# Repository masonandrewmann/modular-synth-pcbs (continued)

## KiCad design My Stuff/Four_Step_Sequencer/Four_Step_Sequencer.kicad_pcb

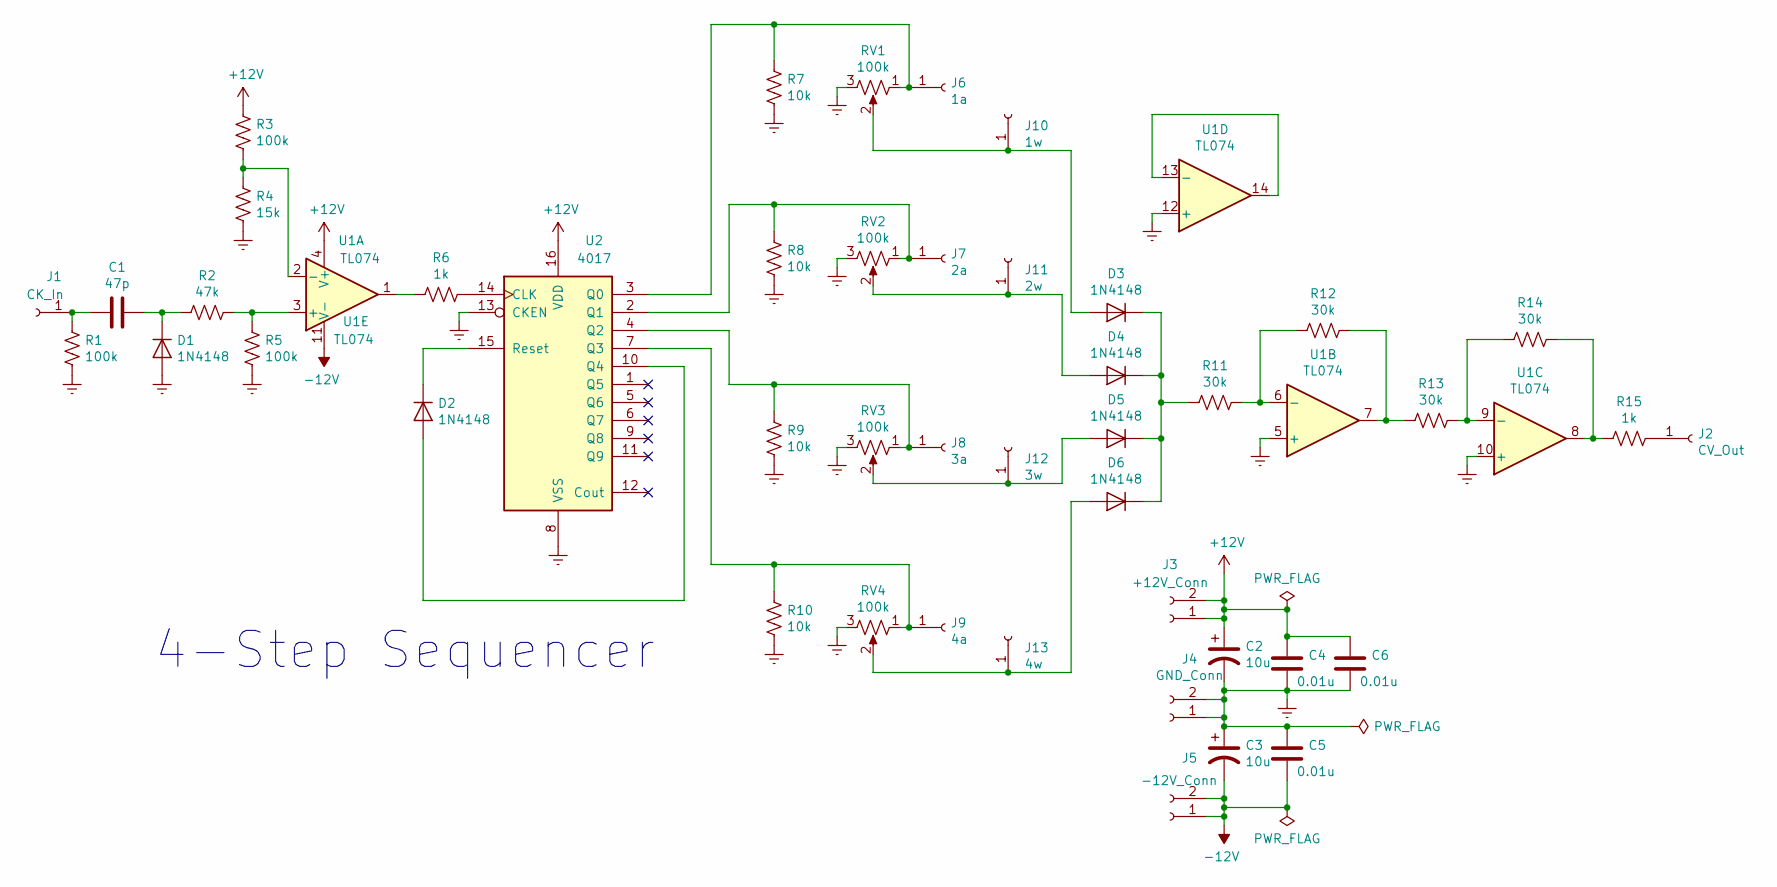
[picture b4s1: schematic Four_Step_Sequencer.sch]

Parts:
C1: 47p; C_Rect_L7.0mm_W2.5mm_P5.00mm
C2, C3: 10u; CP_Radial_D6.3mm_P2.50mm
C4, C5, C6: 0.01u; C_Rect_L7.0mm_W2.5mm_P5.00mm
D1, D2, D3, D4, D5, D6: 1N4148; D_T-1_P5.08mm_Horizontal
J1: CK_In; SolderWirePad_1x01_Drill1mm
J2: CV_Out; SolderWirePad_1x01_Drill1mm
J3: +12V_Conn; SolderWirePad_1x02_P3.81mm_Drill1mm
J4: GND_Conn; SolderWirePad_1x02_P3.81mm_Drill1mm
J5: -12V_Conn; SolderWirePad_1x02_P3.81mm_Drill1mm
J6: 1a; SolderWirePad_1x01_Drill1mm
J7: 2a; SolderWirePad_1x01_Drill1mm
J8: 3a; SolderWirePad_1x01_Drill1mm
J9: 4a; SolderWirePad_1x01_Drill1mm
J10: 1w; SolderWirePad_1x01_Drill1mm
J11: 2w; SolderWirePad_1x01_Drill1mm
J12: 3w; SolderWirePad_1x01_Drill1mm
J13: 4w; SolderWirePad_1x01_Drill1mm
R1, R3, R5: 100k; R_Axial_DIN0207_L6.3mm_D2.5mm_P7.62mm_Horizontal
R2: 47k; R_Axial_DIN0207_L6.3mm_D2.5mm_P7.62mm_Horizontal
R4: 15k; R_Axial_DIN0207_L6.3mm_D2.5mm_P7.62mm_Horizontal
R6, R15: 1k; R_Axial_DIN0207_L6.3mm_D2.5mm_P7.62mm_Horizontal
R7, R8, R9, R10: 10k; R_Axial_DIN0207_L6.3mm_D2.5mm_P7.62mm_Horizontal
R11, R12, R13, R14: 30k; R_Axial_DIN0207_L6.3mm_D2.5mm_P7.62mm_Horizontal
RV1, RV2, RV3, RV4: 100k
U1: TL074; DIP-14_W7.62mm_Socket
U2: 4017; DIP-16_W7.62mm_Socket

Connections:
+12V: C2.1, C4.1, C6.1, J3.1, J3.2, R3.1, U1.4 (V+), U2.16 (VDD)
-12V: C3.2, C5.2, J5.1, J5.2, U1.11 (V-)
Earth: C2.2, C3.1, C4.2, C5.1, C6.2, D1.2 (A), J4.1, J4.2, R1.1, R4.2, R5.2, R7.2, R8.2, R9.2, R10.2, RV1.3, RV2.3, RV3.3, RV4.3, U1.5 (+), U1.10 (+), U1.12 (+), U2.8 (VSS), U2.13 (CKEN)
unnamed: C1.1, D1.1 (K), R2.1
unnamed: C1.2, J1.1, R1.2
unnamed: D2.1 (K), U2.15 (Reset)
unnamed: D2.2 (A), U2.10 (Q4)
unnamed: D3.1 (K), D4.1 (K), D5.1 (K), D6.1 (K), R11.2
unnamed: D3.2 (A), J10.1, RV1.2
unnamed: D4.2 (A), J11.1, RV2.2
unnamed: D5.2 (A), J12.1, RV3.2
unnamed: D6.2 (A), J13.1, RV4.2
unnamed: J2.1, R15.1
unnamed: J6.1, R7.1, RV1.1, U2.3 (Q0)
unnamed: J7.1, R8.1, RV2.1, U2.2 (Q1)
unnamed: J8.1, R9.1, RV3.1, U2.4 (Q2)
unnamed: J9.1, R10.1, RV4.1, U2.7 (Q3)
unnamed: R2.2, R5.1, U1.3 (+)
unnamed: R3.2, R4.1, U1.2 (-)
unnamed: R6.1, U1.1
unnamed: R6.2, U2.14 (CLK)
unnamed: R11.1, R12.2, U1.6 (-)
unnamed: R12.1, R13.2, U1.7
unnamed: R13.1, R14.2, U1.9 (-)
unnamed: R14.1, R15.2, U1.8
unnamed: U1.13 (-), U1.14

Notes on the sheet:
4-Step Sequencer

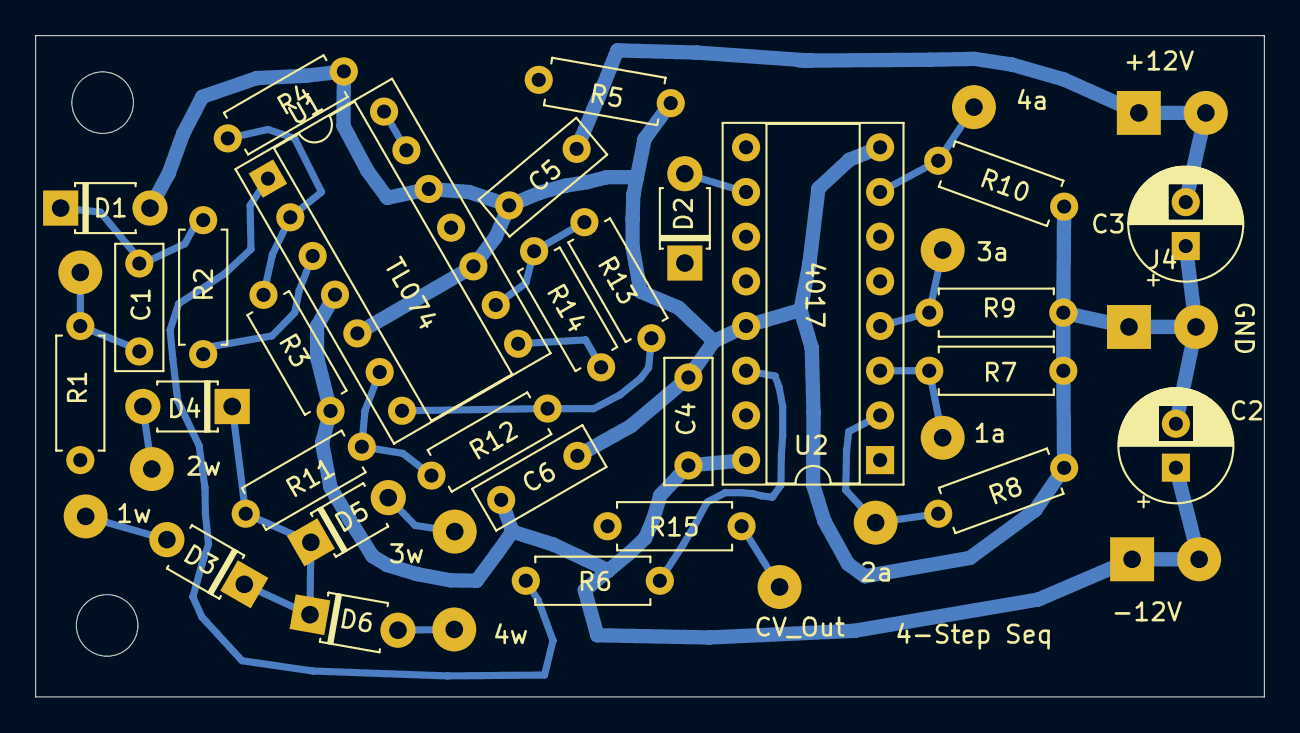
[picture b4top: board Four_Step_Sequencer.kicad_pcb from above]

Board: 2 copper layers, 69.8 x 37.6 mm, 42 parts (0 on the bottom side), 26 nets.

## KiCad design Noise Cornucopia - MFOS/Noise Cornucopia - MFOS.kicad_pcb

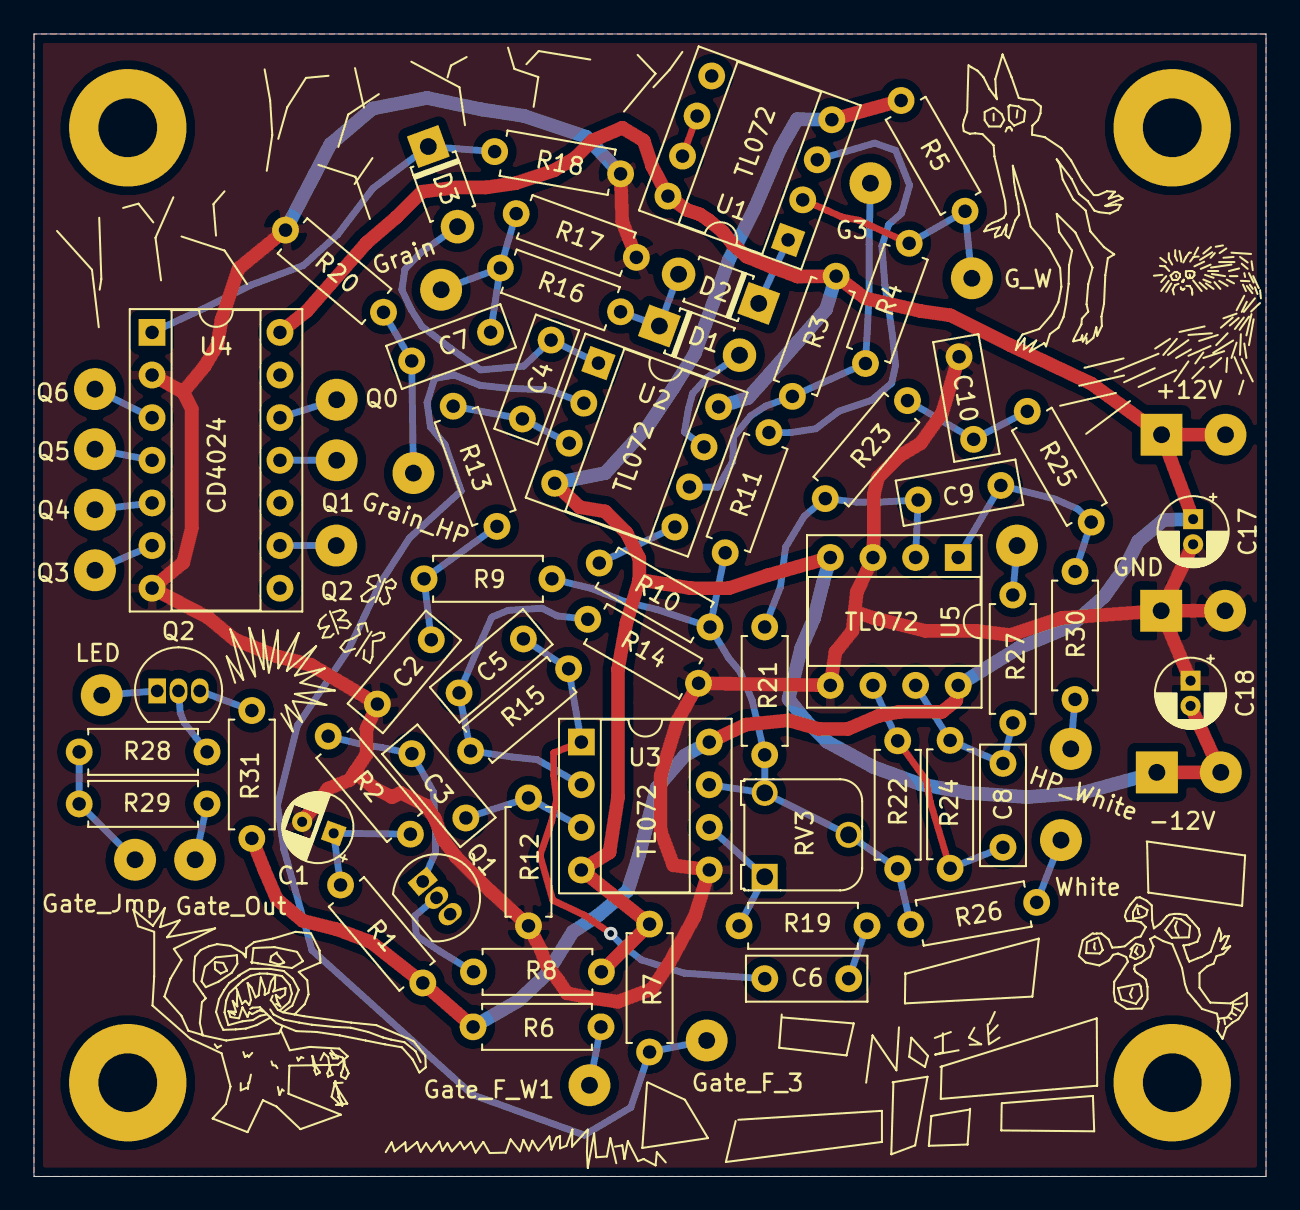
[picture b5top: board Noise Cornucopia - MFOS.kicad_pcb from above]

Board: 2 copper layers, 73.4 x 68.1 mm, 76 parts (0 on the bottom side), 48 nets.

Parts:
C1: 1u; CP_Radial_D4.0mm_P2.00mm
C2: 0.0047u; C_Rect_L7.0mm_W2.5mm_P5.00mm
C3, C6: 0.1u; C_Rect_L7.0mm_W2.5mm_P5.00mm
C4, C5: 10p; C_Rect_L7.0mm_W2.5mm_P5.00mm
C7, C8: 0.001u; C_Rect_L7.0mm_W2.5mm_P5.00mm
C9: 100p; C_Rect_L7.0mm_W2.5mm_P5.00mm
C10: 0.01u; C_Rect_L7.0mm_W2.5mm_P5.00mm
C17, C18: 10u; CP_Radial_D4.0mm_P1.50mm
D1, D2, D3: D; D_T-1_P5.08mm_Horizontal
J1: GRNS_3; SolderWirePad_1x01_Drill1mm
J2: GRNS_W1; SolderWirePad_1x01_Drill1mm
J3: Gate_F_W1; SolderWirePad_1x01_Drill1mm
J4: Gate_F_3; SolderWirePad_1x01_Drill1mm
J5: Grain; SolderWirePad_1x01_Drill1mm
J6: Grain_HP; SolderWirePad_1x01_Drill1mm
J7: Q0; SolderWirePad_1x01_Drill1mm
J8: Q1; SolderWirePad_1x01_Drill1mm
J9: Q2; SolderWirePad_1x01_Drill1mm
J10: Q3; SolderWirePad_1x01_Drill1mm
J11: Q4; SolderWirePad_1x01_Drill1mm
J12: Q5; SolderWirePad_1x01_Drill1mm
J13: Q6; SolderWirePad_1x01_Drill1mm
J14: GATE_JMP; SolderWirePad_1x01_Drill1mm
J15: White; SolderWirePad_1x01_Drill1mm
J16: LP_White; SolderWirePad_1x01_Drill1mm
J17: GATE_OUT; SolderWirePad_1x01_Drill1mm
J18: HP_White; SolderWirePad_1x01_Drill1mm
J19: LED; SolderWirePad_1x01_Drill1mm
J20: +12V_Conn; SolderWirePad_1x02_P3.81mm_Drill1mm
J21: GND_Conn?; SolderWirePad_1x02_P3.81mm_Drill1mm
J22: -12V_Conn; SolderWirePad_1x02_P3.81mm_Drill1mm
Q1, Q2: 2N3904; TO-92_Inline
R1, R2, R15, R21: 470k; R_Axial_DIN0207_L6.3mm_D2.5mm_P7.62mm_Horizontal
R3, R5, R6, R28: 47k; R_Axial_DIN0207_L6.3mm_D2.5mm_P7.62mm_Horizontal
R4: 200k; R_Axial_DIN0207_L6.3mm_D2.5mm_P7.62mm_Horizontal
R7, R9, R13, R18: 20k; R_Axial_DIN0207_L6.3mm_D2.5mm_P7.62mm_Horizontal
R8, R10, R11, R14, R19: 10k; R_Axial_DIN0207_L6.3mm_D2.5mm_P7.62mm_Horizontal
R12: 2M; R_Axial_DIN0207_L6.3mm_D2.5mm_P7.62mm_Horizontal
R16, R17, R20, R31: 4k7; R_Axial_DIN0207_L6.3mm_D2.5mm_P7.62mm_Horizontal
R22: 100k; R_Axial_DIN0207_L6.3mm_D2.5mm_P7.62mm_Horizontal
R23, R25: 43k; R_Axial_DIN0207_L6.3mm_D2.5mm_P7.62mm_Horizontal
R24: 1M; R_Axial_DIN0207_L6.3mm_D2.5mm_P7.62mm_Horizontal
R26, R27, R29, R30: 1k; R_Axial_DIN0207_L6.3mm_D2.5mm_P7.62mm_Horizontal
RV3: 500k; Potentiometer_Runtron_RM-065_Vertical
U1, U2, U3, U5: TL072; DIP-8_W7.62mm_Socket
U4: 4024; DIP-14_W7.62mm_Socket

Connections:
+12V: C17.1, J20.1, J20.2, R1.1, R3.2, R6.2, R31.2, U1.8, U2.8, U3.8, U4.14, U5.8
-12V: C18.2, J22.1, J22.2, R5.1, R7.1, R8.2, U1.4, U2.4, U3.4, U5.4
Earth: C1.2, C2.2, C10.1, C17.2, C18.1, J21.1, J21.2, R12.2, R14.2, R17.1, R18.1, R20.1, U3.5, U4.2, U4.7, U5.3, U5.5
unnamed: C1.1, R1.2, R2.1
unnamed: C2.1, R9.1, R13.1
unnamed: C3.1, R12.1, U3.3
unnamed: C3.2, Q1.1, R2.2
unnamed: C4.1, D3.2, U2.1
unnamed: C4.2, R13.2, U2.3
unnamed: C5.1, C6.2, R15.1, U3.1
unnamed: C5.2, R14.1, R15.2, U3.2
unnamed: C6.1, R19.2
unnamed: C7.1, J6.1, R20.2
unnamed: C7.2, J5.1, R16.1, R17.2
unnamed: C8.1, R24.1, R27.2, U5.7
unnamed: C8.2, R22.1, R24.2, U5.6
unnamed: C9.1, R25.1, R30.2, U5.1
unnamed: C9.2, R21.1, R23.2, U5.2
unnamed: C10.2, R23.1, R25.2
unnamed: D1.1, D2.2, R16.2
unnamed: D1.2, U2.7
unnamed: D2.1, U1.1
unnamed: D3.1, R18.2, U4.1
unnamed: J19.1, Q2.1
unnamed: J1.1, R3.1, R4.2, U2.6
unnamed: J2.1, R4.1, R5.2, U1.2
unnamed: J3.1, R6.1
unnamed: J4.1, R7.2, U2.2
unnamed: J7.1, U4.12
unnamed: J8.1, U4.11
unnamed: J9.1, U4.9
unnamed: J10.1, U4.6
unnamed: J11.1, U4.5
unnamed: J12.1, U4.4
unnamed: J13.1, U4.3
unnamed: J14.1, R28.1, R29.1
unnamed: J15.1, R26.1
unnamed: J16.1, R27.1
unnamed: J17.1, R29.2
unnamed: J18.1, R30.1
unnamed: Q1.2, R8.1
unnamed: Q2.2, R28.2
unnamed: Q2.3, R31.1
unnamed: R10.1, U2.5
unnamed: R9.2, R10.2, R11.2, R21.2, R22.2, R26.2, RV3.2, RV3.3, U3.7
unnamed: R11.1, U1.3
unnamed: R19.1, RV3.1, U3.6
unnamed: U1.6, U1.7

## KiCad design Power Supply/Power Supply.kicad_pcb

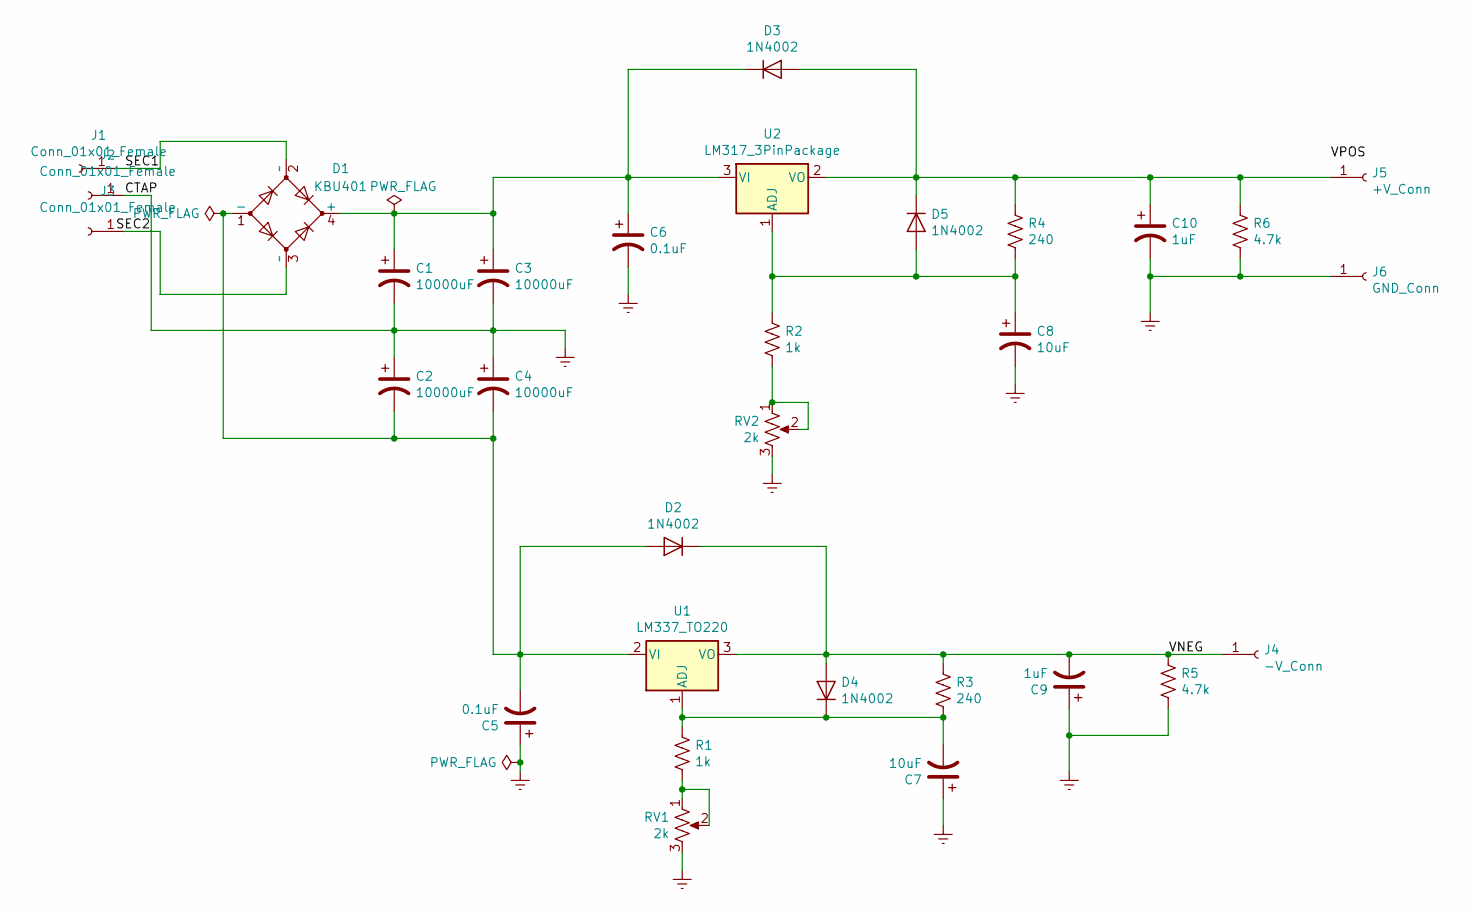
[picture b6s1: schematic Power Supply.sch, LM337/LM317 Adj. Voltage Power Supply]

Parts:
C1, C2, C3, C4: 10000uF; CP_Radial_D30.0mm_P10.00mm_SnapIn
C5, C6: 0.1uF; CP_Radial_D5.0mm_P2.50mm
C7, C8: 10uF; CP_Radial_D5.0mm_P2.50mm
C9, C10: 1uF; CP_Radial_D5.0mm_P2.50mm
D1: KBU401; Diode_Bridge_Vishay_KBU
D2, D3, D4, D5: 1N4002; D_DO-41_SOD81_P10.16mm_Horizontal
J1, J2, J3: Conn_01x01_Female; Pin_D1.1mm_L10.2mm_W3.5mm_Flat
J4: -V_Conn; Pin_D1.1mm_L10.2mm_W3.5mm_Flat
J5: +V_Conn; Pin_D1.1mm_L10.2mm_W3.5mm_Flat
J6: GND_Conn; Pin_D1.1mm_L10.2mm_W3.5mm_Flat
R1, R2: 1k; R_Axial_DIN0207_L6.3mm_D2.5mm_P7.62mm_Horizontal
R3, R4: 240; R_Axial_DIN0207_L6.3mm_D2.5mm_P7.62mm_Horizontal
R5, R6: 4.7k; R_Axial_DIN0207_L6.3mm_D2.5mm_P7.62mm_Horizontal
RV1, RV2: 2k; Potentiometer_Runtron_RM-065_Vertical
U1: LM337_TO220; TO-220-3_Horizontal_TabUp_WIDE
U2: LM317_3PinPackage; TO-220-3_Horizontal_TabDown_WIDE

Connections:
/SEC1: D1.2 (~~), J1.1
/VNEG: C9.2, D2.1 (K), D4.2 (A), J4.1, R3.1, R5.1, U1.3 (VO)
Earth: C1.2, C2.1, C3.2, C4.1, C5.1, C6.2, C7.1, C8.2, C9.1, C10.2, J2.1, J6.1, R5.2, R6.2, RV1.3, RV2.3
unnamed: C1.1, C3.1, C6.1, D1.4 (+), D3.1 (K), U2.3 (VI)
unnamed: C2.2, C4.2, C5.2, D1.1 (-), D2.2 (A), U1.2 (VI)
unnamed: C7.2, D4.1 (K), R1.1, R3.2, U1.1 (ADJ)
unnamed: C8.1, D5.2 (A), R2.1, R4.2, U2.1 (ADJ)
unnamed: C10.1, D3.2 (A), D5.1 (K), J5.1, R4.1, R6.1, U2.2 (VO)
unnamed: D1.3 (~~), J3.1
unnamed: R1.2, RV1.1, RV1.2
unnamed: R2.2, RV2.1, RV2.2

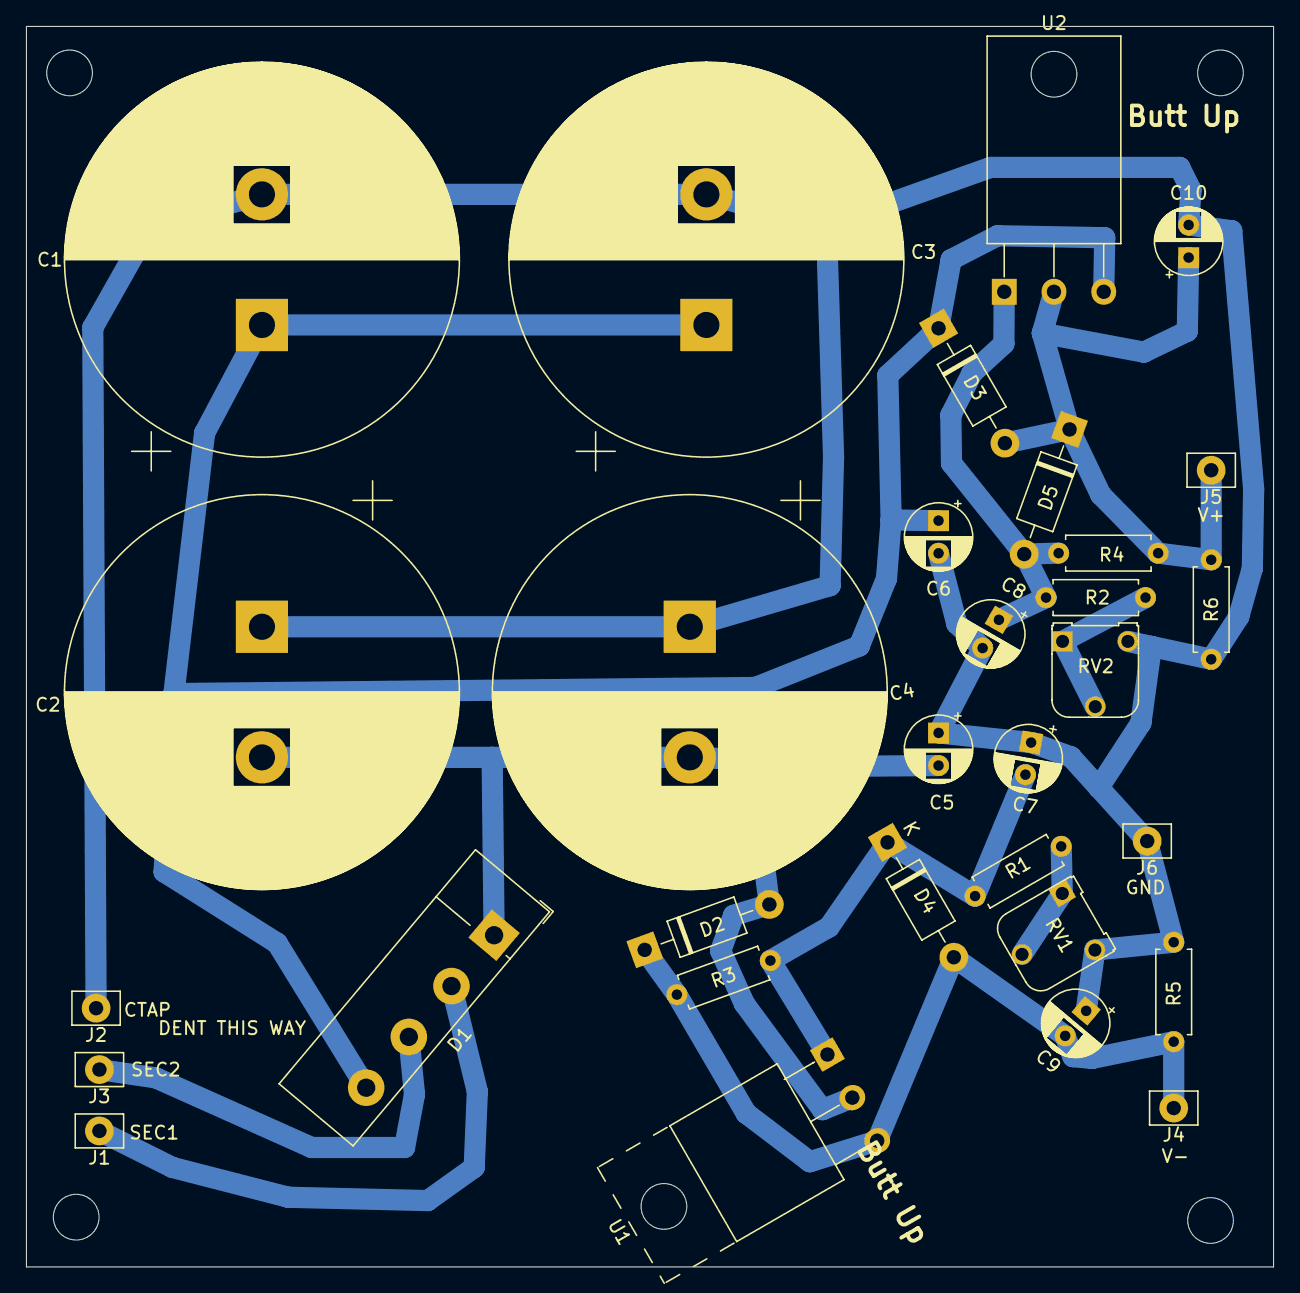
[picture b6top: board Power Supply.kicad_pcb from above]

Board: 2 copper layers, 95.5 x 95.0 mm, 31 parts (0 on the bottom side), 11 nets.

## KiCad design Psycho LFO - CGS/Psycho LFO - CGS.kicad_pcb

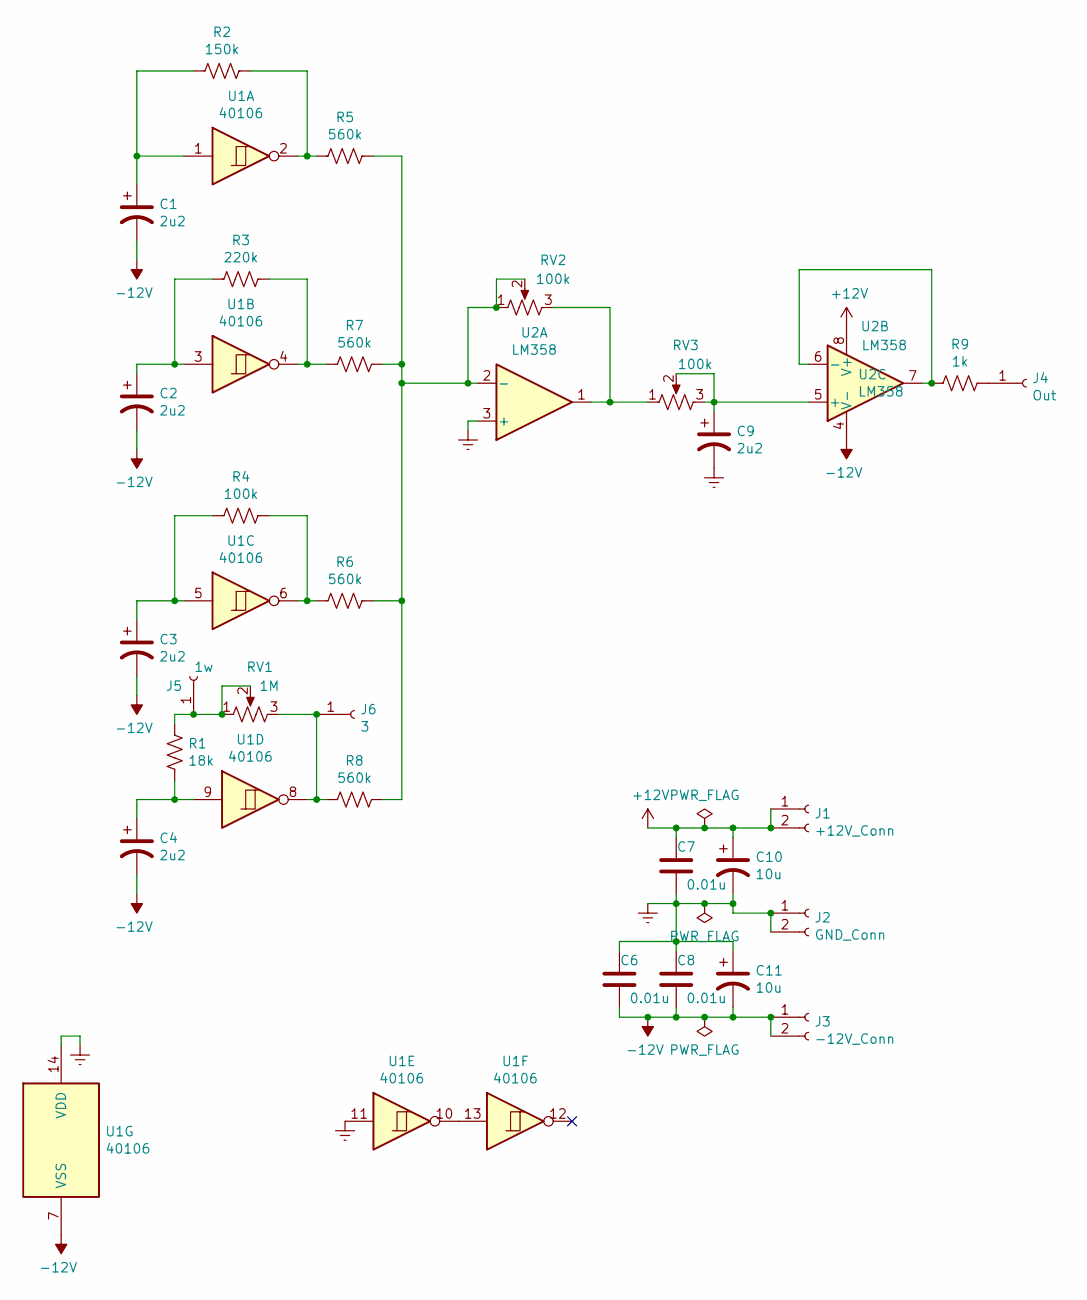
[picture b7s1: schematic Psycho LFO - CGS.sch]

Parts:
C1, C2, C3, C4, C9: 2u2; CP_Radial_D5.0mm_P2.50mm
C6, C7, C8: 0.01u; C_Rect_L7.0mm_W2.5mm_P5.00mm
C10, C11: 10u; CP_Radial_D6.3mm_P2.50mm
J1: +12V_Conn; SolderWirePad_1x02_P3.81mm_Drill1mm
J2: GND_Conn; SolderWirePad_1x02_P3.81mm_Drill1mm
J3: -12V_Conn; SolderWirePad_1x02_P3.81mm_Drill1mm
J4: Out; SolderWirePad_1x01_Drill1mm
J5: 1w; SolderWirePad_1x01_Drill1mm
J6: 3; SolderWirePad_1x01_Drill1mm
R1: 18k; R_Axial_DIN0207_L6.3mm_D2.5mm_P7.62mm_Horizontal
R2: 150k; R_Axial_DIN0207_L6.3mm_D2.5mm_P7.62mm_Horizontal
R3: 220k; R_Axial_DIN0207_L6.3mm_D2.5mm_P7.62mm_Horizontal
R4: 100k; R_Axial_DIN0207_L6.3mm_D2.5mm_P7.62mm_Horizontal
R5, R6, R7, R8: 560k; R_Axial_DIN0207_L6.3mm_D2.5mm_P7.62mm_Horizontal
R9: 1k; R_Axial_DIN0207_L6.3mm_D2.5mm_P7.62mm_Horizontal
RV1: 1M
RV2, RV3: 100k
U1: 40106; DIP-14_W7.62mm_Socket
U2: LM358; DIP-8_W7.62mm_Socket

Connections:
+12V: C7.1, C10.1, J1.1, J1.2, U2.8 (V+)
-12V: C1.2, C2.2, C3.2, C4.2, C6.2, C8.2, C11.2, J3.1, J3.2, U1.7 (VSS), U2.4 (V-)
Earth: C6.1, C7.2, C8.1, C9.2, C10.2, C11.1, J2.1, J2.2, U1.11, U1.14 (VDD), U2.3 (+)
unnamed: C1.1, R2.2, U1.1
unnamed: C2.1, R3.2, U1.3
unnamed: C3.1, R4.2, U1.5
unnamed: C4.1, R1.1, U1.9
unnamed: C9.1, RV3.2, RV3.3, U2.5 (+)
unnamed: J4.1, R9.1
unnamed: J5.1, R1.2, RV1.1, RV1.2
unnamed: J6.1, R8.2, RV1.3, U1.8
unnamed: R2.1, R5.2, U1.2
unnamed: R3.1, R7.2, U1.4
unnamed: R4.1, R6.2, U1.6
unnamed: R5.1, R6.1, R7.1, R8.1, RV2.1, RV2.2, U2.2 (-)
unnamed: R9.2, U2.6 (-), U2.7
unnamed: RV2.3, RV3.1, U2.1
unnamed: U1.10, U1.13

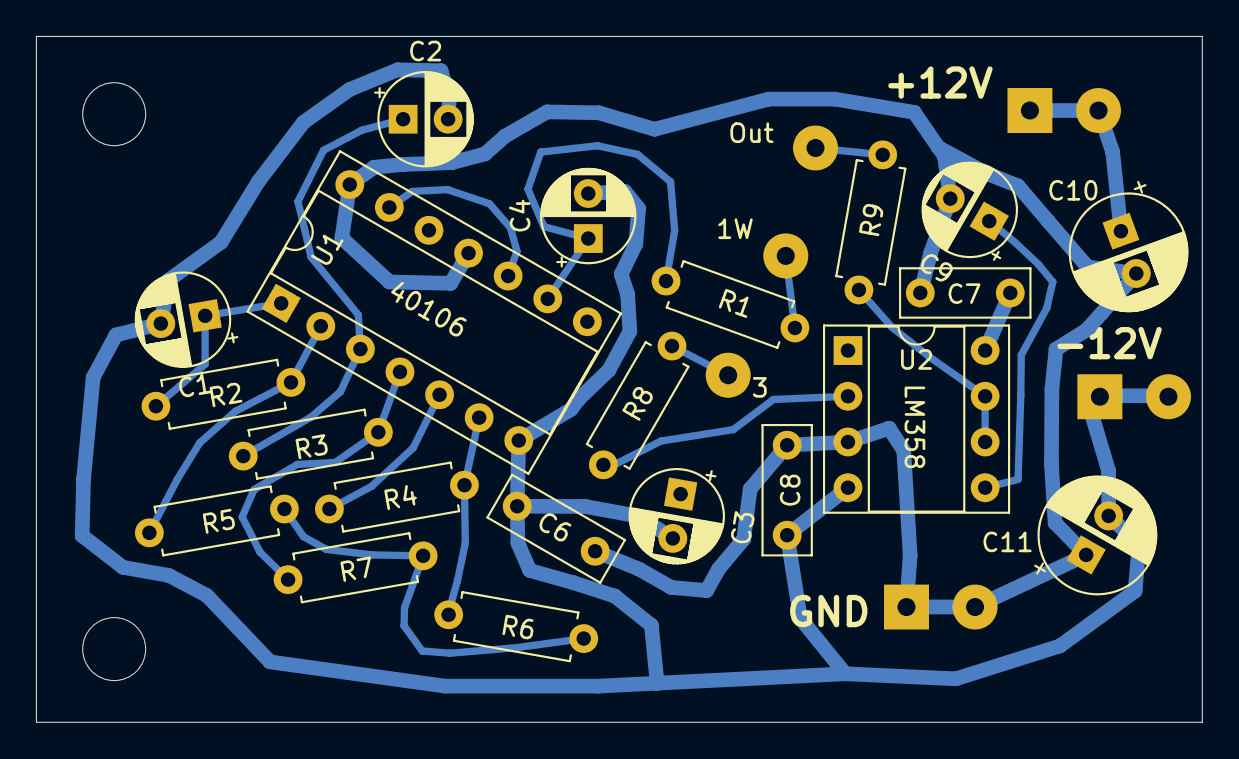
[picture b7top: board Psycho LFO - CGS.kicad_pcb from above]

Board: 2 copper layers, 64.8 x 38.1 mm, 27 parts (0 on the bottom side), 17 nets.

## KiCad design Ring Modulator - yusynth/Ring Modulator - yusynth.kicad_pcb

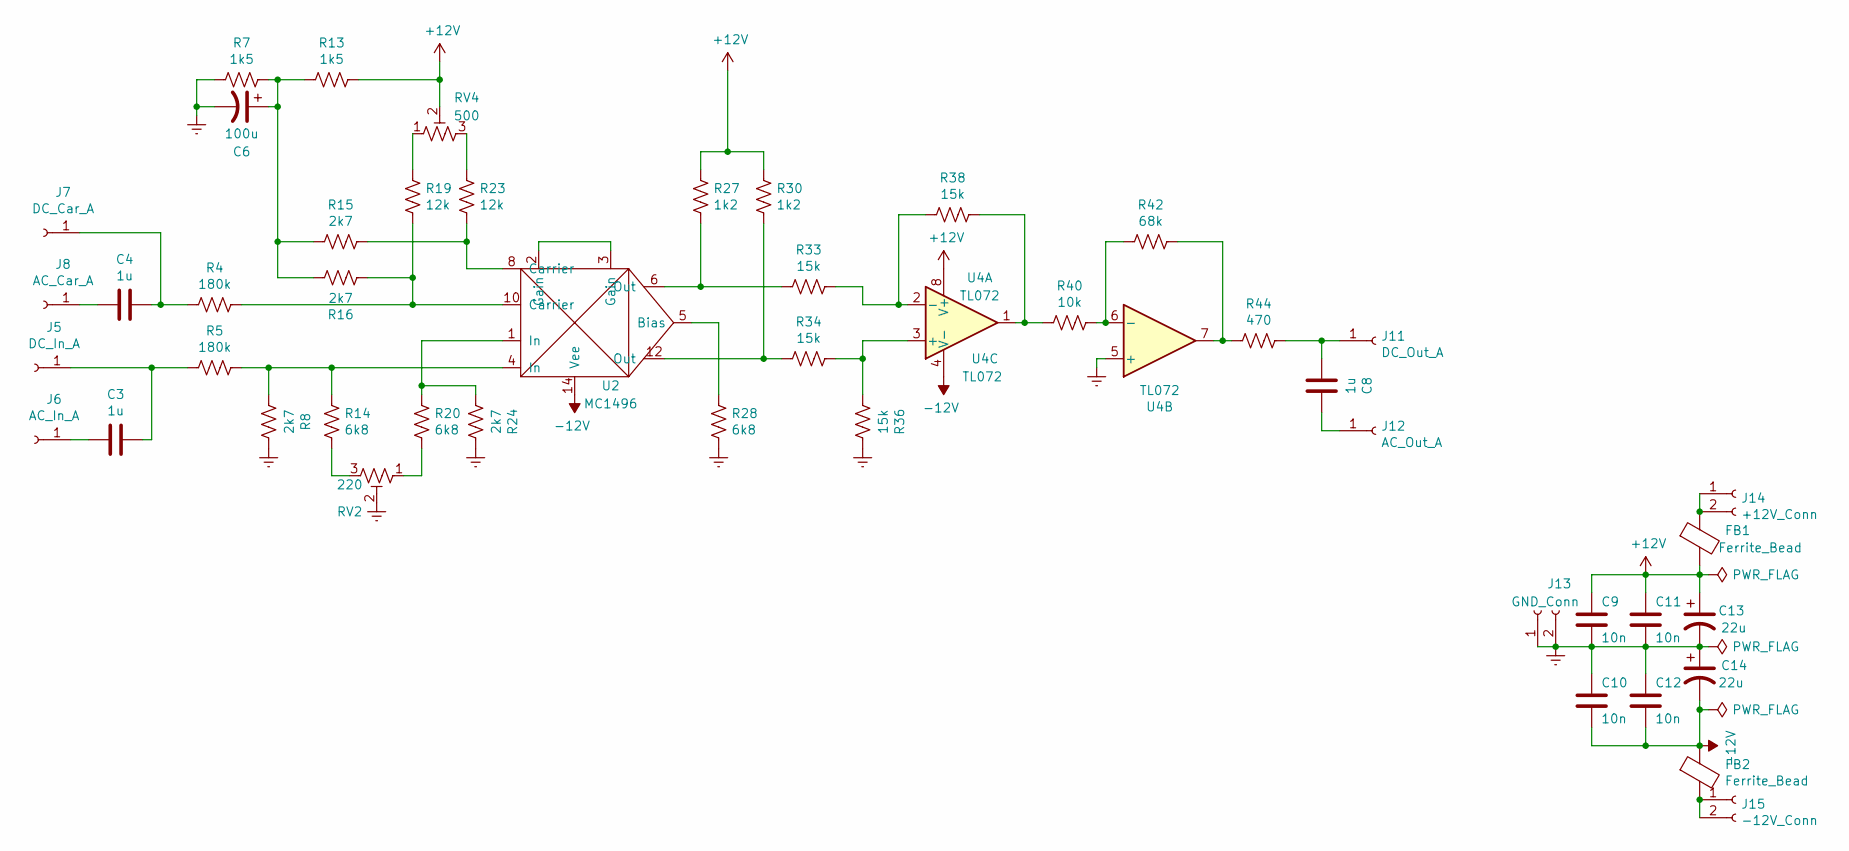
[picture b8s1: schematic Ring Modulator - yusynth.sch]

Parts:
C3, C4: 1u; C_0603_1608Metric; LCSC C15849
C6: 100u; CP_Radial_D6.3mm_P2.50mm
C8: 1u; C_0603_1608Metric; JLCPCB LCSC
C9, C10, C11, C12: 10n; C_0603_1608Metric; LCSC C57112
C13, C14: 22u; CP_Radial_D6.3mm_P2.50mm
FB1, FB2: Ferrite_Bead; L_Axial_L7.0mm_D3.3mm_P10.16mm_Horizontal_Fastron_MICC
J5: DC_In_A; SolderWirePad_1x01_Drill1mm
J6: AC_In_A; SolderWirePad_1x01_Drill1mm
J7: DC_Car_A; SolderWirePad_1x01_Drill1mm
J8: AC_Car_A; SolderWirePad_1x01_Drill1mm
J11: DC_Out_A; SolderWirePad_1x01_Drill1mm
J12: AC_Out_A; SolderWirePad_1x01_Drill1mm
J13: GND_Conn; SolderWirePad_1x02_P3.81mm_Drill1mm
J14: +12V_Conn; SolderWirePad_1x02_P3.81mm_Drill1mm
J15: -12V_Conn; SolderWirePad_1x02_P3.81mm_Drill1mm
R4, R5: 180k; R_0603_1608Metric; LCSC C22827
R7, R13: 1k5; R_0603_1608Metric; LCSC C22843
R8, R15, R16, R24: 2k7; R_0603_1608Metric; LCSC C13167
R14, R20, R28: 6k8; R_0603_1608Metric; LCSC C23212
R19, R23: 12k; R_0603_1608Metric; LCSC C22790
R27, R30: 1k2; R_0603_1608Metric; LCSC C22765
R33, R34, R36, R38: 15k; R_0603_1608Metric; LCSC C22809
R40: 10k; R_0603_1608Metric; LCSC C25804
R42: 68k; R_0603_1608Metric; LCSC C23231
R44: 470; R_0603_1608Metric; LCSC C23179
RV2: 220; Potentiometer_Runtron_RM-065_Vertical
RV4: 500; Potentiometer_Runtron_RM-065_Vertical
U2: MC1496; DIP-14_W7.62mm_Socket
U4: TL072; SOIC-8_3.9x4.9mm_P1.27mm; LCSC C6961

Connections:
+12V: C9.1, C11.1, C13.1, FB1.2, R13.2, R27.1, R30.1, RV4.2, U4.8 (V+)
-12V: C10.2, C12.2, C14.2, FB2.1, U2.14 (Vee), U4.4 (V-)
Earth: C6.2, C9.2, C10.1, C11.2, C12.1, C13.2, C14.1, J13.1, J13.2, R7.1, R8.1, R24.1, R28.2, R36.1, RV2.2, U4.5 (+)
unnamed: C3.1, J5.1, R5.2
unnamed: C3.2, J6.1
unnamed: C4.1, J7.1, R4.2
unnamed: C4.2, J8.1
unnamed: C6.1, R7.2, R13.1, R15.2, R16.1
unnamed: C8.1, J12.1
unnamed: C8.2, J11.1, R44.1
unnamed: FB1.1, J14.1, J14.2
unnamed: FB2.2, J15.1, J15.2
unnamed: R5.1, R8.2, R14.1, U2.4 (In)
unnamed: R14.2, RV2.3
unnamed: R15.1, R23.1, U2.8 (Carrier)
unnamed: R4.1, R16.2, R19.1, U2.10 (Carrier)
unnamed: R19.2, RV4.1
unnamed: R20.1, R24.2, U2.1 (In)
unnamed: R20.2, RV2.1
unnamed: R23.2, RV4.3
unnamed: R27.2, R33.2, U2.6 (Out)
unnamed: R28.1, U2.5 (Bias)
unnamed: R30.2, R34.2, U2.12 (Out)
unnamed: R33.1, R38.2, U4.2 (-)
unnamed: R34.1, R36.2, U4.3 (+)
unnamed: R38.1, R40.2, U4.1
unnamed: R40.1, R42.2, U4.6 (-)
unnamed: R42.1, R44.2, U4.7
unnamed: U2.2 (Gain), U2.3 (Gain)

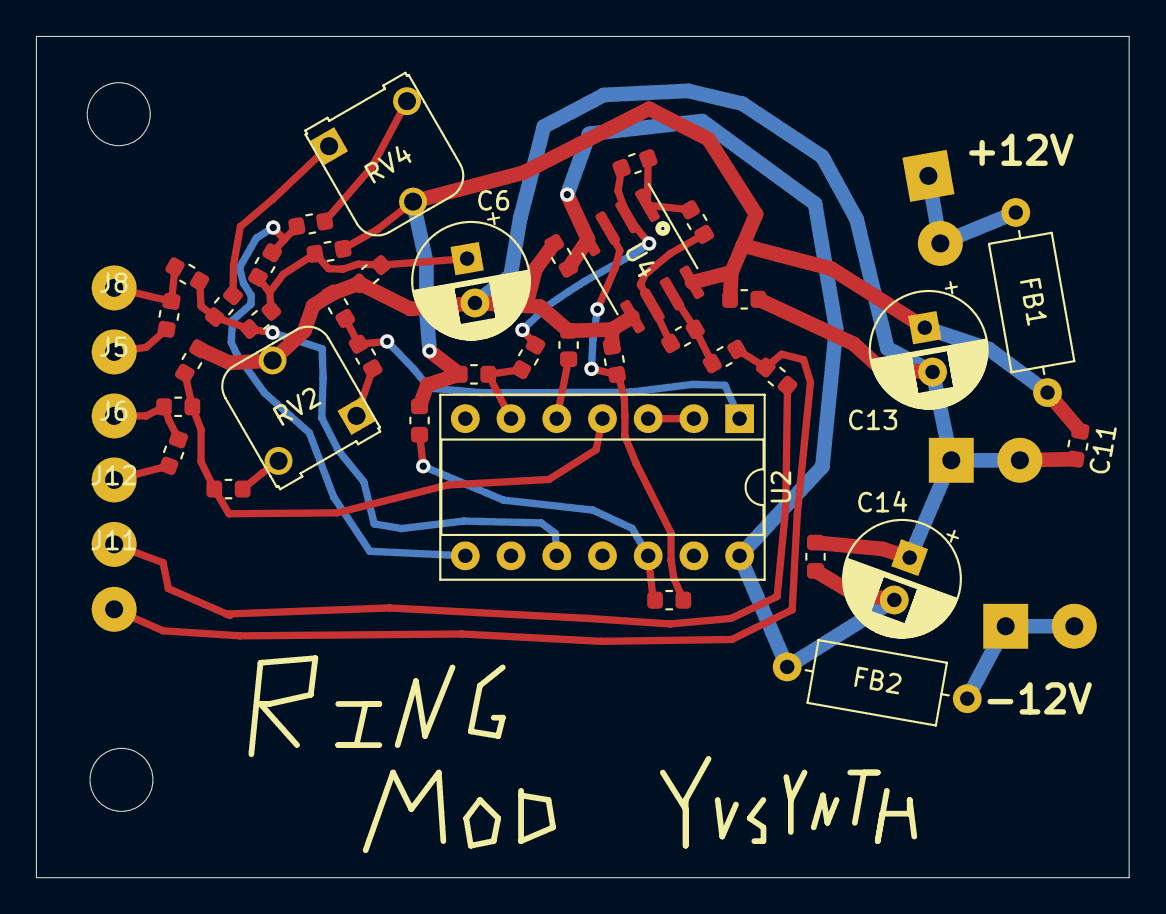
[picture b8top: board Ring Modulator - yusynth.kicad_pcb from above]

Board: 2 copper layers, 60.7 x 46.7 mm, 47 parts (0 on the bottom side), 29 nets.
